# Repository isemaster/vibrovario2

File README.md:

# VibroVario2 - Watchy V3 with BMP390 Integration

## Overview
This is a modified version of the Watchy V3.0 board with integrated BMP390 barometric pressure sensor for variometer applications.

## Changes from Original Watchy V3.0

### Added Components
1. **BMP390** (U5) - Barometric Pressure Sensor
   - Package: LGA-10 (2.0x2.0x0.75mm)
   - I2C Address: 0x77 (SDO tied to GND)
   - Position: Near ESP32-S3

2. **Decoupling Capacitors** (per BMP390 datasheet)
   - C22: 100nF (0402) - High-frequency decoupling
   - C23: 1uF (0402) - Bulk decoupling

### Pin Connections
| BMP390 Pin | Function | ESP32-S3 GPIO | Net Name |
|------------|----------|---------------|----------|
| 1 | GND | - | GND |
| 2 | VDDIO | - | +3V3 |
| 3 | SDO | - | GND (sets I2C addr 0x77) |
| 4 | INT2 | - | NC |
| 5 | VDD | GPIO45 | BMP390_PWR |
| 6 | INT1 | - | NC |
| 7 | SCL | GPIO11 | SCL |
| 8 | SDA | GPIO12 | SDA |
| 9 | CSB | - | +3V3 (I2C mode) |
| 10 | GND | - | GND |

### Power Control
- BMP390 VDD is connected to GPIO45 for power management
- Set GPIO45 HIGH to enable BMP390
- Set GPIO45 LOW to disable BMP390 (power saving mode)

## Files Structure
```
vibrovario2/
├── vibrovario2.kicad_sch    # Schematic with BMP390
├── vibrovario2.kicad_pcb    # PCB with BMP390 placed
├── vibrovario2.kicad_pro    # Project file
├── BMP390.kicad_sym         # BMP390 symbol library
├── vibrovario2.lib          # Legacy symbol library
├── sym-lib-table            # Symbol library table
├── vibrovario2.pretty/      # Footprint library
│   └── BMP390_LGA-10.kicad_mod
└── README.md
```

## Assembly Notes
1. BMP390 is a small LGA-10 package (2x2mm) - requires precise soldering
2. Recommend using solder paste and hot air reflow for BMP390
3. Decoupling capacitors should be placed close to BMP390 VDD pin
4. All components are SMD for factory assembly

## Firmware Integration
For Arduino/PlatformIO:

```cpp
#include <Wire.h>
#include <Adafruit_BMP3XX.h>

#define BMP390_SDA 12
#define BMP390_SCL 11
#define BMP390_PWR 45

Adafruit_BMP3XX bmp;

void setup() {
  // Enable BMP390 power
  pinMode(BMP390_PWR, OUTPUT);
  digitalWrite(BMP390_PWR, HIGH);
  delay(10);  // Wait for power stabilization

  // Initialize I2C
  Wire.begin(BMP390_SDA, BMP390_SCL);

  // Initialize BMP390
  if (!bmp.begin_I2C(0x77)) {
    Serial.println("BMP390 not found!");
    while (1);
  }

  // Configure for variometer use
  bmp.setTemperatureOversampling(BMP3_OVERSAMPLING_8X);
  bmp.setPressureOversampling(BMP3_OVERSAMPLING_4X);
  bmp.setIIRFilterCoeff(BMP3_IIR_FILTER_COEFF_3);
  bmp.setOutputDataRate(BMP3_ODR_25_HZ);
}

void loop() {
  if (bmp.performReading()) {
    float altitude = bmp.readAltitude(1013.25);
    Serial.printf("Altitude: %.2f m\n", altitude);
  }
  delay(100);
}
```

## BOM Additions
| Reference | Value | Package | Manufacturer | MPN | LCSC |
|-----------|-------|---------|--------------|-----|------|
| U5 | BMP390 | LGA-10 | Bosch | BMP390 | C496091 |
| C22 | 100nF | 0402 | Samsung | CL05B104JB5NNNC | C1525 |
| C23 | 1uF | 0402 | Samsung | CL05A105KA5NQNC | C52923 |

## License
Based on Watchy by SQFMI (https://sqfmi.com/watchy)
Original hardware design: MIT License

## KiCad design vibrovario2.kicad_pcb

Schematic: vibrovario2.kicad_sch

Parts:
AE1: Antenna_Chip; SWRA117D
C1, C10: 10uF; C_0402_1005Metric
C2, C3, C4, C15: 1uF; C_0402_1005Metric
C5, C6, C11, C12, C13, C14: 100nF; C_0402_1005Metric
C7, C9: 3pF; C_0402_1005Metric
C16, C19: 26pF; C_0402_1005Metric
C17, C18: 10pF; C_0402_1005Metric
C20, C21: 4.7uF/50V; C_0603_1608Metric
C22, C23, C24, C25, C26, C27, C28, C29: 1uF/50V; C_0402_1005Metric
D1, D3, D4, D5: MBR0530; D_SOD-123
D2: 1N4001; D_SOD-123F
J1: Battery; 1.25T-2PWT (Molex 532610271)
J2: Micro USB; USB_Micro-B
J3: FPC24(0.5MM); 24_Pins_0.5mm_Pitch_ZIF_Connector_UP
L1: 7.5nH; L_0402_1005Metric
L2: 47uH 0.5A; L_Taiyo-Yuden_NR-40xx
M1: Vibration_Motor; Motor_Header
Q1: CJ2301; SOT-23
Q2: S8050; SOT-23
Q3: AO3400A; SOT-23
R1, R3, R18, R20: 10K; R_0402_1005Metric
R2, R4, R6, R7, R8, R10, R11, R15, R19: 100K; R_0402_1005Metric
R5, R14: 51K; R_0402_1005Metric
R9: 360K; R_0402_1005Metric
R12, R16: 1M; R_0402_1005Metric
R13: 1K; R_0402_1005Metric
R17: 2.2; R_0402_1005Metric
SW1: BTN2; EVQPUC
SW2: BTN1; EVQPUC
SW3: BTN3; EVQPUC
SW4: BTN4; EVQPUC
TP1: TX; TestPoint_Pad_D1.0mm
TP2: RX; TestPoint_Pad_D1.0mm
TP3: BOOT; TestPoint_Pad_D1.0mm
TP4: 3V3; TestPoint_Pad_D1.0mm
TP5: GND; TestPoint_Pad_D1.0mm
TP6: SCL; TestPoint_Pad_D1.0mm
TP7: SDA; TestPoint_Pad_D1.0mm
U1: SR2HARU
U2: RT908033; SOT-23-5
U3: TP4054; SOT-23-5
U4: ESP32-S3; QFN-56-1EP_7x7mm_P0.4mm_EP5.6x5.6mm
U5: USBLC6-2P6; SOT-666
U6: BMA423; LGA-12_2x2mm_P0.5mm
Y1: 32.768KHz; Crystal_SMD_2012-2Pin_2.0x1.2mm
Y2: 40MHz; Crystal_SMD_2520-4Pin_2.5x2.0mm

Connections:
+3V3: C1.1, C3.1, C4.1, C5.1, C6.1, C10.1, C14.1, C20.1, C28.1, D2.1 (K), J3.15, J3.16, L2.2, M1.1 (+), R1.2, R4.2, R7.2, R10.2, R11.2, R18.2, R19.1, R20.2, TP4.1, U1.6 (VCC), U2.5 (VOUT), U4.2 (VDD3P3), U4.3 (VDD3P3), U4.20 (VDD3P3_RTC), U4.46 (VDD3P3_CPU), U4.55 (VDDA), U4.56 (VDDA), U6.3 (VDDIO), U6.7 (VDD), U6.10 (CSB); also elsewhere on the board
+BATT: J1.1, Q1.3 (D), R8.1, U3.3 (VBAT)
/32K_N: C18.1, U4.22 (GPIO16/ADC2_CH5/XTAL_32K_N), Y1.2
/32K_P: C17.1, U4.21 (GPIO15/ADC2_CH4/XTAL_32K_P), Y1.1
/40M_P: C16.1, R12.2, Y2.1
ACC_INT_1: U4.19 (GPIO14/ADC2_CH3), U6.5 (INT1)
ACC_INT_2: U4.18 (GPIO13/ADC2_CH2), U6.6 (INT2)
ADC: C11.1, R8.2, R9.1, U4.14 (GPIO9/ADC1_CH8)
BMP390_PWR: U4.51 (GPIO45); also elsewhere on the board
BTN1: R4.1, SW2.1 (A), U4.12 (GPIO7/ADC1_CH6)
BTN2: R7.1, SW1.1 (A), U1.2 (~SR1), U4.11 (GPIO6/ADC1_CH5)
BTN3: R10.1, SW3.1 (A), TP3.1, U1.5 (~SR0), U4.5 (GPIO0/BOOT)
BTN4: R11.1, SW4.1 (A), U4.13 (GPIO8/ADC1_CH7)
BUSY: J3.9, U4.41 (GPIO36)
CS: J3.12, U4.38 (GPIO33)
DC: J3.11, U4.39 (GPIO34)
DN: J2.2 (D-), U5.4 (I/O2)
DP: J2.3 (D+), U5.6 (I/O1)
EN: C2.1, R1.1, U1.3 (~RST), U4.4 (CHIP_PU/RESET)
GDR: J3.2, Q3.1 (G), R16.1
MOSI: J3.14, U4.36 (SPICLK_N/GPIO48)
unnamed: AE1.1 (FEED), C7.1, L1.1
unnamed: D1.1 (K), Q1.2 (S), U2.1 (VIN), U2.3 (EN)
unnamed: C14.2, D2.2 (A), M1.2 (-), Q2.3 (C)
unnamed: C21.1, D3.1 (K), D4.2 (A)
unnamed: C21.2, D5.2 (A), L2.1, Q3.3 (D)
unnamed: C23.1, J3.5
unnamed: C24.1, J3.18
unnamed: C25.1, J3.20
unnamed: C26.1, J3.22
unnamed: C27.1, J3.24
unnamed: Q2.1 (B), R13.1
unnamed: R3.2, U3.5 (PROG)
unnamed: R6.2, U3.1 (STAT)
unnamed: C9.1, L1.2, U4.1 (LNA_IN/RF)
unnamed: TP2.1, U4.50 (U0RXD/PROG/GPIO44)
unnamed: TP1.1, U4.49 (U0TXD/PROG/GPIO43)
unnamed: R12.1, U4.54 (XTAL_P)
PREVGH: C22.1, D5.1 (K), J3.21
PREVGL: C29.2, D3.2 (A), J3.23
RES: J3.10, R19.2, U4.40 (GPIO35)
RESE: J3.3, Q3.2 (S), R17.2
SCK: J3.13, U4.37 (SPICLK_P/GPIO47)
SCL: R20.1, TP6.1, U4.16 (GPIO11/ADC2_CH0), U6.12 (SCX); also elsewhere on the board
SDA: R18.1, TP7.1, U4.17 (GPIO12/ADC2_CH1), U6.2 (SDX); also elsewhere on the board
STAT: R5.2, R6.1, U4.15 (GPIO10/ADC1_CH9)
USB_D+: U4.26 (GPIO20/USB_D+/ADC2_CH9), U5.1 (I/O1)
USB_D-: U4.25 (GPIO19/USB_D-/ADC2_CH8), U5.3 (I/O2)
USB_DET: R14.2, R15.1, U4.27 (GPIO21)
VBUS: C12.1, D1.2 (A), J2.1 (VBUS), Q1.1 (G), R2.1, R5.1, R14.1, U3.4 (VDD), U5.5 (VBUS)
VDD: C13.1, C15.1, U4.29 (VDD_SPI)
VIB_PWM: R13.2, U4.23 (GPIO17/ADC2_CH6/DAC_2)

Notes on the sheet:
Vibration Motor
Buttons
E-Paper Driver
Accelerometer
ESP32-S3
USB
Power & Battery

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
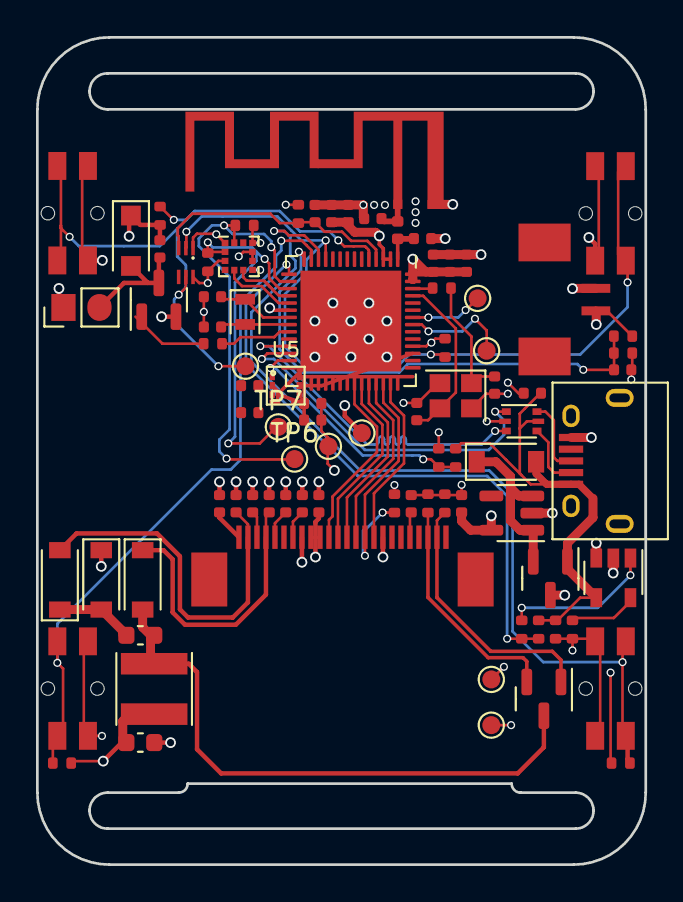
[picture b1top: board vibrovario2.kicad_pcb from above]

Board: 4 copper layers, 33.8 x 46.0 mm, 87 parts (0 on the bottom side), 54 nets.

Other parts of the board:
C22#2: 100nF; C_0402_1005Metric
C23#2: 1uF; C_0402_1005Metric
TP4#2: 3V3; TestPoint_Pad_D1.0mm
TP5#2: GND; TestPoint_Pad_D1.0mm
U5#2: BMP390; BMP390_LGA-10

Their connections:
+3V3: TP4#2.1, U5#2.2 (VDDIO), U5#2.9 (CSB); also elsewhere on the board
BMP390_PWR: C22#2.1, C23#2.1, U5#2.5 (VDD); also elsewhere on the board
SCL: U5#2.7 (SCL); also elsewhere on the board
SDA: U5#2.8 (SDA); also elsewhere on the board

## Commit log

2026-02-14 Create 1
